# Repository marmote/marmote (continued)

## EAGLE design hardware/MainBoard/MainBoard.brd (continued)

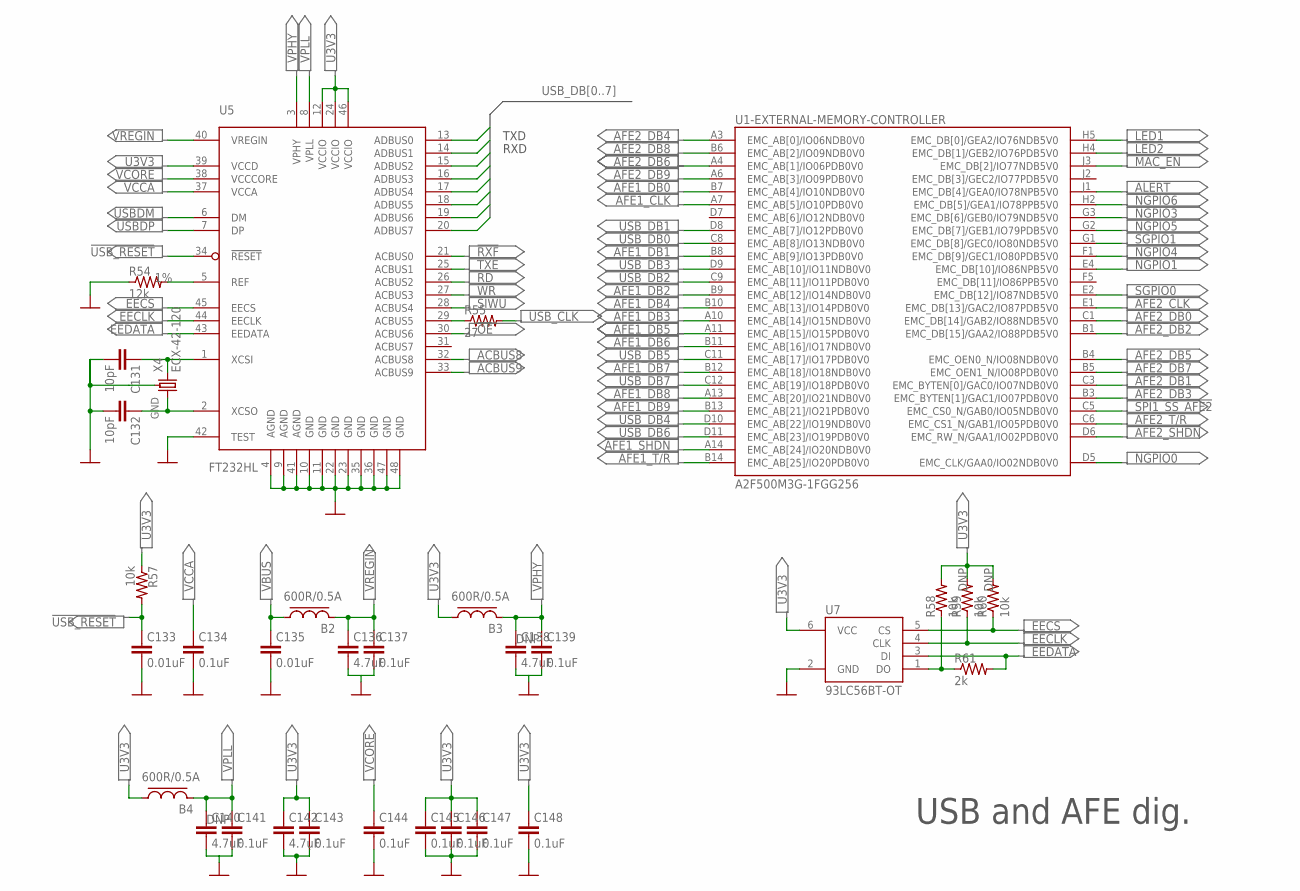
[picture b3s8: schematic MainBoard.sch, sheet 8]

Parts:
B2, B3, B4: 600R/0.5A; L0603; MPN BLM18EG601SN1D; DIGI-KEY# 490-3994-2-ND
C131, C132: 10pF; C0402
C133, C135: 0.01uF; C0402
C134, C137, C139, C141, C143, C144, C145, C146, C147, C148: 0.1uF; C0402
C136, C138, C140, C142: 4.7uF; C0402
R54: 12k; R0402; TOLERANCE 1%
R55: 27; R0402
R57, R58, R59, R60: 10k; R0402
R61: 2k; R0402
U1: A2F500M3G-1FGG256; FG256
U5: FT232HL; LQFP-48; MPN 768-1101-1-ND
U7: 93LC56BT-OT; SOT23-6L
X4: ECX-42-120; ECX-42

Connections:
!AFE1_SHDN: U1.A14 (EMC_AB[24]/IO20NDB0V0); also elsewhere on the board
!AFE2_SHDN: U1.D6 (EMC_RW_N/GAA1/IO02PDB0V0); also elsewhere on the board
!OE: U5.30 (ACBUS6); also elsewhere on the board
!RD: U5.26 (ACBUS2); also elsewhere on the board
!RXF: U5.21 (ACBUS0); also elsewhere on the board
!SIWU: U5.28 (ACBUS4); also elsewhere on the board
!SPI1_SS_AFE2: U1.C5 (EMC_CS0_N/GAB0/IO05NDB0V0); also elsewhere on the board
!TXE: U5.25 (ACBUS1); also elsewhere on the board
!USB_RESET: C133.1, R57.2, U5.34 (!RESET)
!WR: U5.27 (ACBUS3); also elsewhere on the board
ACBUS8: U5.32 (ACBUS8); also elsewhere on the board
ACBUS9: U5.33 (ACBUS9); also elsewhere on the board
AFE1_CLK: U1.A7 (EMC_AB[5]/IO10PDB0V0); also elsewhere on the board
AFE1_DB0: U1.B7 (EMC_AB[4]/IO10NDB0V0); also elsewhere on the board
AFE1_DB1: U1.B8 (EMC_AB[9]/IO13PDB0V0); also elsewhere on the board
AFE1_DB2: U1.B9 (EMC_AB[12]/IO14NDB0V0); also elsewhere on the board
AFE1_DB3: U1.A10 (EMC_AB[14]/IO15NDB0V0); also elsewhere on the board
AFE1_DB4: U1.B10 (EMC_AB[13]/IO14PDB0V0); also elsewhere on the board
AFE1_DB5: U1.A11 (EMC_AB[15]/IO15PDB0V0); also elsewhere on the board
AFE1_DB6: U1.B11 (EMC_AB[16]/IO17NDB0V0); also elsewhere on the board
AFE1_DB7: U1.B12 (EMC_AB[18]/IO18NDB0V0); also elsewhere on the board
AFE1_DB8: U1.A13 (EMC_AB[20]/IO21NDB0V0); also elsewhere on the board
AFE1_DB9: U1.B13 (EMC_AB[21]/IO21PDB0V0); also elsewhere on the board
AFE1_T/!R: U1.B14 (EMC_AB[25]/IO20PDB0V0); also elsewhere on the board
AFE2_CLK: U1.E1 (EMC_DB[13]/GAC2/IO87PDB5V0); also elsewhere on the board
AFE2_DB0: U1.C1 (EMC_DB[14]/GAB2/IO88NDB5V0); also elsewhere on the board
AFE2_DB1: U1.C3 (EMC_BYTEN[0]/GAC0/IO07NDB0V0); also elsewhere on the board
AFE2_DB2: U1.B1 (EMC_DB[15]/GAA2/IO88PDB5V0); also elsewhere on the board
AFE2_DB3: U1.B3 (EMC_BYTEN[1]/GAC1/IO07PDB0V0); also elsewhere on the board
AFE2_DB4: U1.A3 (EMC_AB[0]/IO06NDB0V0); also elsewhere on the board
AFE2_DB5: U1.B4 (EMC_OEN0_N/IO08NDB0V0); also elsewhere on the board
AFE2_DB6: U1.A4 (EMC_AB[1]/IO06PDB0V0); also elsewhere on the board
AFE2_DB7: U1.B5 (EMC_OEN1_N/IO08PDB0V0); also elsewhere on the board
AFE2_DB8: U1.B6 (EMC_AB[2]/IO09NDB0V0); also elsewhere on the board
AFE2_DB9: U1.A6 (EMC_AB[3]/IO09PDB0V0); also elsewhere on the board
AFE2_T/!R: U1.C6 (EMC_CS1_N/GAB1/IO05PDB0V0); also elsewhere on the board
ALERT: U1.J1 (EMC_DB[4]/GEA0/IO78NPB5V0); also elsewhere on the board
DGND: C131.2, C132.2, C133.2, C134.2, C135.2, C136.2, C137.2, C138.2, C139.2, C140.2, C141.2, C142.2, C143.2, C144.2, C145.2, C146.2, C147.2, C148.2, R54.1, U5.4 (AGND), U5.9 (AGND), U5.10 (GND), U5.11 (GND), U5.22 (GND), U5.23 (GND), U5.35 (GND), U5.36 (GND), U5.41 (AGND), U5.42 (TEST), U5.47 (GND), U5.48 (GND), U7.2 (GND), X4.2 (GND), X4.4 (GND); also elsewhere on the board
EECLK: R59.1, U5.44 (EECLK), U7.4 (CLK)
EECS: R60.1, U5.45 (EECS), U7.5 (CS)
EEDATA: R61.2, U5.43 (EEDATA), U7.3 (DI)
EEDO: R58.1, R61.1, U7.1 (DO)
LED1: U1.H5 (EMC_DB[0]/GEA2/IO76NDB5V0); also elsewhere on the board
LED2: U1.H4 (EMC_DB[1]/GEB2/IO76PDB5V0); also elsewhere on the board
MAC_EN: U1.J3 (EMC_DB[2]/IO77NDB5V0); also elsewhere on the board
NGPIO0: U1.D5 (EMC_CLK/GAA0/IO02NDB0V0); also elsewhere on the board
NGPIO1: U1.E4 (EMC_DB[10]/IO86NPB5V0); also elsewhere on the board
NGPIO3: U1.G3 (EMC_DB[6]/GEB0/IO79NDB5V0); also elsewhere on the board
NGPIO4: U1.F1 (EMC_DB[9]/GEC1/IO80PDB5V0); also elsewhere on the board
NGPIO5: U1.G2 (EMC_DB[7]/GEB1/IO79PDB5V0); also elsewhere on the board
NGPIO6: U1.H2 (EMC_DB[5]/GEA1/IO78PPB5V0); also elsewhere on the board
SGPIO0: U1.E2 (EMC_DB[12]/IO87NDB5V0); also elsewhere on the board
SGPIO1: U1.G1 (EMC_DB[8]/GEC0/IO80NDB5V0); also elsewhere on the board
U3V3: B3.1, B4.1, C142.1, C143.1, C145.1, C146.1, C147.1, C148.1, R57.1, R58.2, R59.2, R60.2, U5.12 (VCCIO), U5.24 (VCCIO), U5.39 (VCCD), U5.46 (VCCIO), U7.6 (VCC)
UREF: R54.2, U5.5 (REF)
USBDM: U5.6 (DM); also elsewhere on the board
USBDP: U5.7 (DP); also elsewhere on the board
USB_CLK: R55.2; also elsewhere on the board
USB_CLKF: R55.1, U5.29 (ACBUS5)
USB_DB0: U1.C8 (EMC_AB[8]/IO13NDB0V0), U5.13 (ADBUS0); also elsewhere on the board
USB_DB1: U1.D8 (EMC_AB[7]/IO12PDB0V0), U5.14 (ADBUS1); also elsewhere on the board
USB_DB2: U1.C9 (EMC_AB[11]/IO11PDB0V0), U5.15 (ADBUS2)
USB_DB3: U1.D9 (EMC_AB[10]/IO11NDB0V0), U5.16 (ADBUS3)
USB_DB4: U1.D10 (EMC_AB[22]/IO19NDB0V0), U5.17 (ADBUS4)
USB_DB5: U1.C11 (EMC_AB[17]/IO17PDB0V0), U5.18 (ADBUS5)
USB_DB6: U1.D11 (EMC_AB[23]/IO19PDB0V0), U5.19 (ADBUS6)
USB_DB7: U1.C12 (EMC_AB[19]/IO18PDB0V0), U5.20 (ADBUS7)
UXCSI: C131.1, U5.1 (XCSI), X4.3 (2)
UXCSO: C132.1, U5.2 (XCSO), X4.1
VBUS: B2.1, C135.1; also elsewhere on the board
VCCA: C134.1, U5.37 (VCCA)
VCORE: C144.1, U5.38 (VCCCORE)
VPHY: B3.2, C138.1, C139.1, U5.3 (VPHY)
VPLL: B4.2, C140.1, C141.1, U5.8 (VPLL)
VREGIN: B2.2, C136.1, C137.1, U5.40 (VREGIN)

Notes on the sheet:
TXD
RXD

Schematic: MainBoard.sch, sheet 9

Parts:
LED1: LED-MGC-3010; LED1208-RA
LED2: LED-ECK-3010; LED1208-RA
R62, R63, R64, R65: 39; R0402
R66, R72, R73: 100; R0402
R67: 330; R0402
R68, R69: 100k; R0402
R70, R71: 4.7k; R0402
U1: A2F500M3G-1FGG256; FG256

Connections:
!OE: U1.E16 (GDC0/IO38NDB1V0); also elsewhere on the board
!RD: U1.D14 (GCB2/IO33PDB1V0); also elsewhere on the board
!RXF: U1.D13 (GBB2/IO27NPB1V0); also elsewhere on the board
!SIWU: U1.E14 (GCB1/IO34PDB1V0); also elsewhere on the board
!SPI1_SS_AFE1: U1.C14 (GBA2/IO27PPB1V0); also elsewhere on the board
!TXE: U1.D15 (IO33NDB1V0); also elsewhere on the board
!WR: U1.E15 (GDC1/IO38PDB1V0); also elsewhere on the board
ACBUS8: U1.E12 (GCA1/IO36PDB1V0); also elsewhere on the board
ACBUS9: U1.F12 (GCA0/IO36NDB1V0); also elsewhere on the board
D3V3: R66.2, R67.2, R68.2, R69.2, R70.2, R71.2; also elsewhere on the board
I2C0_SCL: R70.1, R72.2; also elsewhere on the board
I2C0_SCLI: R72.1, U1.J12 (I2C_0_SCL/GPIO_23)
I2C0_SDA: R71.1, R73.2; also elsewhere on the board
I2C0_SDAI: R73.1, U1.J13 (I2C_0_SDA/GPIO_22)
LED1: LED1.1 (C); also elsewhere on the board
LED1H: LED1.2 (A), R66.1
LED2: LED2.1 (C); also elsewhere on the board
LED2H: LED2.2 (A), R67.1
NGPIO2: U1.F3 (GFB2/IO85NDB5V0); also elsewhere on the board
NGPIO7: U1.E3 (GFA2/IO85PDB5V0); also elsewhere on the board
REF_CLK+: U1.C15 (GCA2/IO28PDB1V0); also elsewhere on the board
REF_CLK-: U1.C16 (IO28NDB1V0); also elsewhere on the board
SPI0_MISO: U1.M16 (SPI_0_DI/GPIO_17); also elsewhere on the board
SPI0_MOSI: U1.N16 (SPI_0_DO/GPIO_16); also elsewhere on the board
SPI0_SCLK: U1.M15 (SPI_0_CLK/GPIO_18); also elsewhere on the board
SPI0_SS: R68.1, U1.M13 (SPI_0_SS/GPIO_19); also elsewhere on the board
SPI1_MISO: U1.L15 (SPI_1_DI/GPIO_25); also elsewhere on the board
SPI1_MOSI: U1.L12 (SPI_1_DO/GPIO_24); also elsewhere on the board
SPI1_SCLK: U1.L14 (SPI_1_CLK/GPIO_26); also elsewhere on the board
SPI1_SS: R69.1, U1.L13 (SPI_1_SS/GPIO_27); also elsewhere on the board
UART0_RXD: R63.2, U1.K12 (UART_0_RXD/GPIO_21)
UART0_TXD: R62.2, U1.K16 (UART_0_TXD/GPIO_20)
UART1_RXD: R65.1; also elsewhere on the board
UART1_RXDI: R65.2, U1.K15 (UART_1_RXD/GPIO_29)
UART1_TXD: R64.1; also elsewhere on the board
UART1_TXDI: R64.2, U1.K14 (UART_1_TXD/GPIO_28)
USB_CLK: U1.F14 (GCB0/IO34NDB1V0); also elsewhere on the board
USB_DB0: R63.1; also elsewhere on the board
USB_DB1: R62.1; also elsewhere on the board

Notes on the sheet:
ORANGE
GREEN

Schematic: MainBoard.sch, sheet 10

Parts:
J1: CON-ZX62R-B-5P; ZX62R-B-5P
J3: CON-FTSH-105-01-L-DV-K; FTSH-105-01-L-DV-K
J4: CON-71741-2184-BOT; 71742-3003-BOT
J5: CON-71741-2184-TOP; 71741-0002; MPN 71741-0002; DIGI-KEY# WM3498CT-ND
M1, M2, M3, M4: MOUNT-HOLE3.3; 3,3
M5, M6, M7, M8, M9, M10, M11, M12: FIDUCIAL1X2; FIDUCIAL-1X2
R74, R75: 0; R0402
R76: 0; R0603
TP1, TP2: TESTPOINT-YELLOW; TESTPOINT
TP3, TP4: TESTPOINT-GREEN; TESTPOINT
U4: USBLC6-2SC6; SOT23-6L

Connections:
!WAKEUP: J4.27, J5.27; also elsewhere on the board
A1V5: J4.79, J4.80, J5.79, J5.80; also elsewhere on the board
A3V3: J4.81, J4.82, J5.81, J5.82; also elsewhere on the board
ADC1+: J5.46; also elsewhere on the board
ADC1-: J5.44; also elsewhere on the board
ADC2+: J5.52; also elsewhere on the board
ADC2-: J5.50; also elsewhere on the board
ADC3+: J5.70; also elsewhere on the board
ADC3-: J5.68; also elsewhere on the board
ADC4+: J5.76; also elsewhere on the board
ADC4-: J5.74; also elsewhere on the board
AGND: J4.29, J4.30, J4.35, J4.36, J4.41, J4.42, J4.47, J4.48, J4.53, J4.54, J4.59, J4.60, J4.65, J4.66, J4.71, J4.72, J4.77, J4.78, J4.83, J4.84, J5.29, J5.30, J5.35, J5.36, J5.41, J5.42, J5.47, J5.48, J5.53, J5.54, J5.59, J5.60, J5.65, J5.66, J5.71, J5.72, J5.77, J5.78, J5.83, J5.84, R76.2, TP3.1, TP4.1; also elsewhere on the board
ALERT: J4.25, J5.25; also elsewhere on the board
D1V5: J4.7, J4.8, J5.7, J5.8; also elsewhere on the board
D3V3: J4.5, J4.6, J5.5, J5.6; also elsewhere on the board
DAC1+: J5.34; also elsewhere on the board
DAC1-: J5.32; also elsewhere on the board
DAC2+: J5.40; also elsewhere on the board
DAC2-: J5.38; also elsewhere on the board
DAC3+: J5.58; also elsewhere on the board
DAC3-: J5.56; also elsewhere on the board
DAC4+: J5.64; also elsewhere on the board
DAC4-: J5.62; also elsewhere on the board
DGND: J1.5 (GND), J3.2, J3.10, J4.1, J4.2, J4.9, J4.10, J5.1, J5.2, J5.9, J5.10, R76.1, TP1.1, TP2.1, U4.2 (GND); also elsewhere on the board
I2C0_SCL: J4.26, J5.26; also elsewhere on the board
I2C0_SDA: J4.28, J5.28; also elsewhere on the board
NGPIO0: J5.11; also elsewhere on the board
NGPIO1: J5.13; also elsewhere on the board
NGPIO2: J5.15; also elsewhere on the board
NGPIO3: J5.17; also elsewhere on the board
NGPIO4: J5.19; also elsewhere on the board
NGPIO5: J5.21; also elsewhere on the board
NGPIO6: J5.23; also elsewhere on the board
NGPIO7: J5.16; also elsewhere on the board
REF_CLK+: J5.14; also elsewhere on the board
REF_CLK-: J5.12; also elsewhere on the board
SF_ABPS0: J5.75; also elsewhere on the board
SF_ABPS1: J5.73; also elsewhere on the board
SF_ADC0: J5.49; also elsewhere on the board
SF_ADC1: J5.51; also elsewhere on the board
SF_ADC2: J5.55; also elsewhere on the board
SF_ADC3: J5.57; also elsewhere on the board
SF_ADC4: J5.45; also elsewhere on the board
SF_ADC5: J5.43; also elsewhere on the board
SF_ADC6: J5.39; also elsewhere on the board
SF_ADC7: J5.37; also elsewhere on the board
SF_CM0: J5.69; also elsewhere on the board
SF_CM1: J5.63; also elsewhere on the board
SF_DAC0: J5.33; also elsewhere on the board
SF_DAC1: J5.31; also elsewhere on the board
SF_TM0: J5.67; also elsewhere on the board
SF_TM1: J5.61; also elsewhere on the board
SGPIO0: J4.17; also elsewhere on the board
SGPIO1: J4.19; also elsewhere on the board
SPI0_MISO: J4.22; also elsewhere on the board
SPI0_MOSI: J4.20; also elsewhere on the board
SPI0_SCLK: J4.18; also elsewhere on the board
SPI0_SS: J4.24; also elsewhere on the board
SPI1_MISO: J5.22; also elsewhere on the board
SPI1_MOSI: J5.20; also elsewhere on the board
SPI1_SCLK: J5.18; also elsewhere on the board
SPI1_SS: J5.24; also elsewhere on the board
TCK: J3.1; also elsewhere on the board
TDI: J3.9; also elsewhere on the board
TDO: J3.3; also elsewhere on the board
TMS: J3.5; also elsewhere on the board
TRST: J3.8; also elsewhere on the board
UART1_RXD: J4.23; also elsewhere on the board
UART1_TXD: J4.21; also elsewhere on the board
USBDM: R74.2; also elsewhere on the board
USBDM-IN: J1.2 (D-), U4.6 (IO1)
USBDM-OUT: R74.1, U4.1 (IO1)
USBDP: R75.2; also elsewhere on the board
USBDP-IN: J1.3 (D+), U4.4 (IO2)
USBDP-OUT: R75.1, U4.3 (IO2)
VBUS: J1.1 (VBUS), U4.5 (VBUS); also elsewhere on the board
VJTAG: J3.6; also elsewhere on the board
VPUMP: J3.7; also elsewhere on the board
VSUP: J4.3, J4.4, J5.3, J5.4

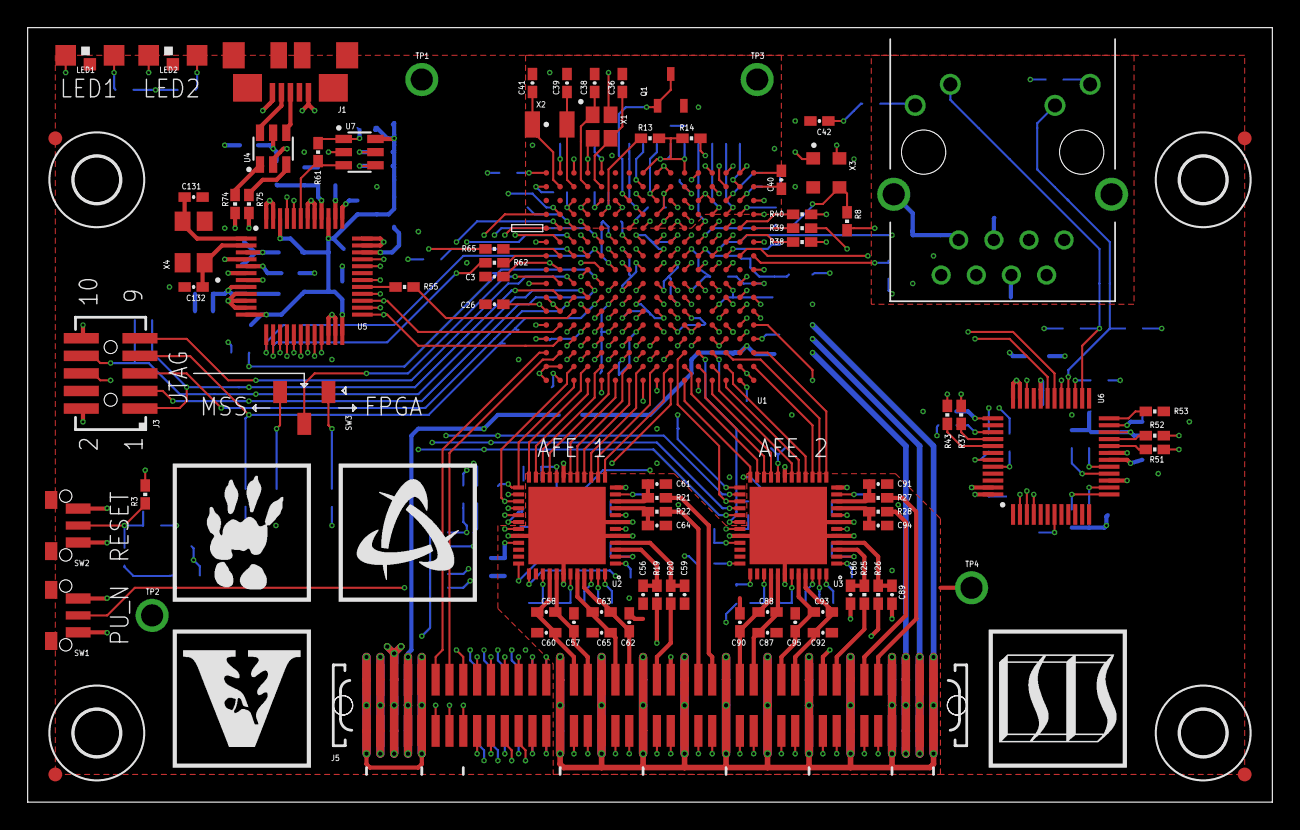
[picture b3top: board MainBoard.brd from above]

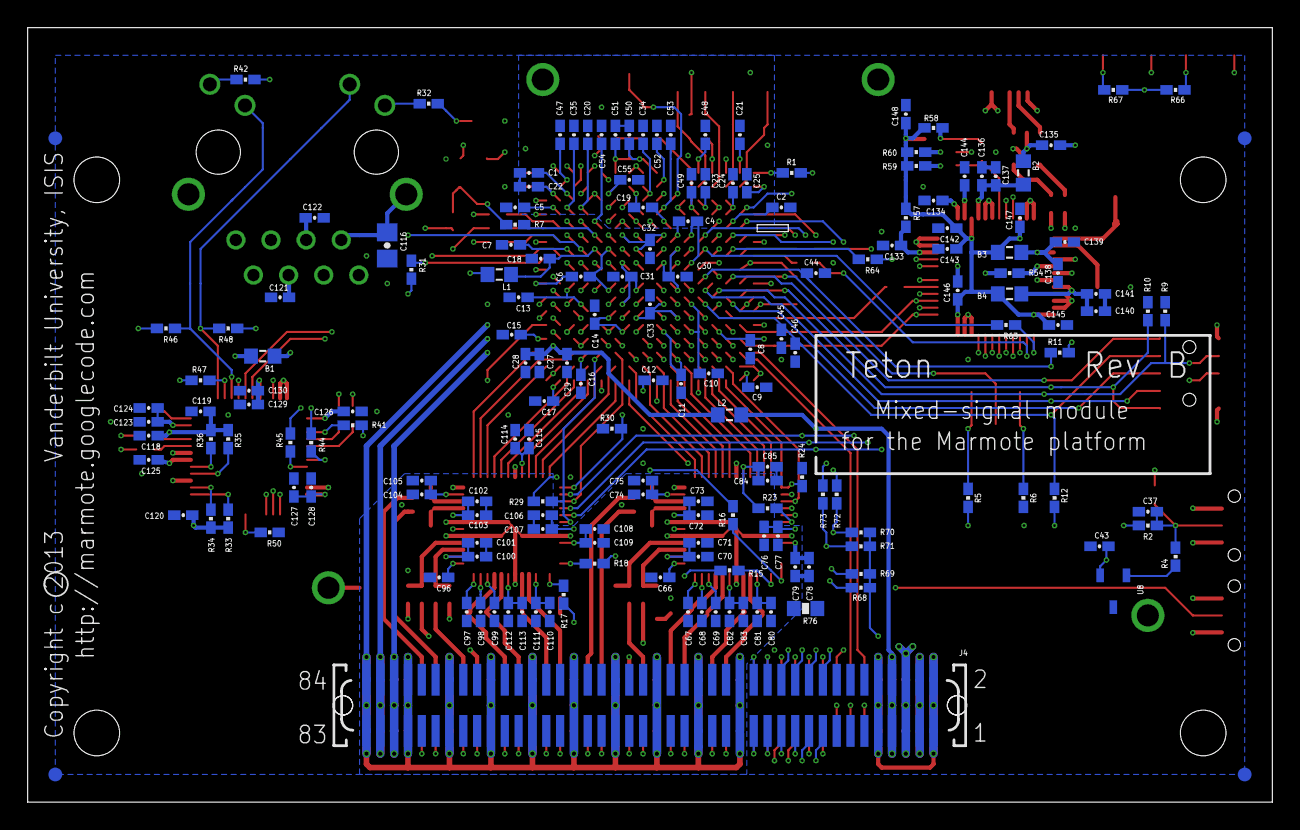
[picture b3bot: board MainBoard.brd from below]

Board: 6 copper layers, 90.0 x 56.0 mm, 270 parts (177 on the bottom side), 221 nets.

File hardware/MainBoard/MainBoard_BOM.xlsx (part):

Bill of Materials for 'Marmote - Main Board (Teton)'
Item # | Reference | Value | Package | Manufacturer | Manufacturer Part # | Supplier | Supplier Part # | Details | Qty | Unit Price | Total Cost
1 | B1 | 70R/4A | BEAD-BLM18SG700TN1D0603 | Murata | BLM18SG700TN1D | Digi-Key | 490-5224-1-ND | FERRITE CHIP 70 OHM 4000MA 0603 | 1 | 0.38 | 0.38
2 | B2, B3, B4 | 600R/0.5A | BEAD-BLM18EG601SN1D0603 | Murata | BLM18EG601SN1D | Digi-Key | 490-3994-2-ND | FILTER CHIP 600 OHM 500MA 0603 | 3 | 0.38 | 1.1400000000000001
3 | C1, C40, C70, C72, C74, C76, C78, C80, C82, C84, C100, C102, C104, C106, C108, 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 | 2.2uF | C0402 | Taiyo Yuden | LMK105BJ225MV-F | Digi-Key | 587-3153-1-ND | CAP CER 2.2UF 10V 20% X5R 0402 | 18 | 0.3 | 5.3999999999999995
4 | C2, C3, C4, C5, C6, C7, C8, C9, C10, C11, C12, C13, C14, C15, C16, C17, C18, C1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 | 0.1uF | C0402 | TDK | C1005X7R1C104K | Digi-Key | 445-4952-1-ND | CAP CER 0.1UF 16V 10% X7R 0402 | 73 | 0.09 | 6.5699999999999994
5 | C29, C42, C46, C133, C135 | 0.01uF | C0402 | TDK | C1005X7R1C103M | Digi-Key | 445-4943-1-ND | CAP CER 10000PF 16V 20% X7R 0402 | 5 | 0.08 | 0.4
6 | C36, C38, C131, C132 | 10pF | C0402 | TDK | C1005C0G1H100D | Digi-Key | 445-1235-1-ND | CAP CER 10PF 50V NP0 0402 | 4 | 0.08 | 0.32
7 | C39, C41 | 4pF | C0402 | TDK | CGA2B2C0G1H040C | Digi-Key | 445-5576-1-ND | CAP CER 4PF 50V NP0 0402 | 2 | 0.2 | 0.4
8 | C45, C66, C67, C68, C96, C97, C98 | 0.33uF | C0402 | TDK | C1005X5R1C334K | Digi-Key | 445-4974-1-ND | CAP CER 0.33UF 16V 10% X5R 0402 | 7 | 0.28000000000000003 | 1.9600000000000002
9 | C47, C48, C52, C53, C54, C55, C57, C58, C60, C62, C63, C65, C87, C88, C90, C92,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 | DNP | C0402 |  |  |  |  | CAPACITOR | 18 |  | 0
10 | C56, C59, C61, C64, C86, C89, C91, C94 | 22pF | C0402 | TDK | C1005C0G1H220J | Digi-Key | 445-1239-1-ND | CAP CER 22PF 50V 5% NP0 0402 | 8 | 0.08 | 0.64
11 | C116 | 1000pF | C0805 | TDK | C2012X7R2E102K | Digi-Key | 445-2277-1-ND | CAP CER 1000PF 250V 10% X7R 0805 | 1 | 0.17 | 0.17
12 | C27, C49, C50, C51, C123, C127, C129, C136, C138, C140, C142 | 4.7uF | C0402 | TDK | C1005X5R1A475M | Digi-Key | 445-8023-1-ND | CAP CER 4.7UF 10V 20% X5R 0402 | 11 | 0.53 | 5.83
13 | J1 | CON-ZX62R-B-5P | CON-ZX62R-B-5P | Hirose | ZX62R-B-5P | Digi-Key | H11574CT-ND | ZX62R-B-5P | 1 | 1.6 | 1.6
14 | J2 | CON-RJ45-J0011D21BNL | CON-RJ45-J0011D21BNL | Pulse Electronics Corporation | J0011D21BNL | Digi-Key | 553-1485-ND | CONN PULSEJACK 1PORT 10/100B-TX | 1 | 7.1 | 7.1
15 | J3 | CON-FTSH-105-01-L-DV-K | CON-FTSH-105-01-L-DV-K | Samtec | FTSH-105-01-L-DV-K | Digi-Key | FTSH-105-01-L-DV-K-ND | CONN HEADER 10 POS DUAL .05" SMD | 1 | 3.45 | 3.45
16 | J4 | CON-71741-2184-BOT | CON-71741-2184-BOT | Molex | 71742-3003 | Digi-Key | WM3499CT-ND | MEZZANINE 1MM BTB RECPT 84CKT | 1 | 5.81 | 5.81
17 | J5 | CON-71741-2184-TOP | CON-71741-2184-TOP | Molex | 71741-0002 | Digi-Key | WM3498CT-ND | MEZZANINE 1MM BTB PLUG 84CKT | 1 | 6.24 | 6.24
18 | L1, L2 | 33nH | L0603 | JW Miller | PM0603-33NJ-RC | Digi-Key | M8487CT-ND | INDUCTOR CHIP 33NH 5% SMD | 2 |  | 0
19 | LED1 | LED-MGC-3010 | LED-MGC-3010 | Kingbright | APECVA3010MGC | Digi-Key | 754-1364-1-ND | LED 3.0X1.0MM 568NM GRN RA SMD | 1 | 0.6 | 0.6
20 | LED2 | LED-ECK-3010 | LED-ECK-3010 | Kingbright | APECVA3010SECK | Digi-Key | 754-1367-1-ND | LED 3X1MM 601NM ORN RA CHIP SMD | 1 | 0.33 | 0.33
21 | Q1 | MMBT3904 | MMBT3904 | Fairchild Semiconductor | MMBT3904 | Digi-Key | MMBT3904FSCT-ND | TRANSISTOR GP NPN AMP SOT-23 | 1 | 0.37 | 0.37
22 | R1, R2, R57, R58, R59, R60 | 10k | R0402 | Rohm | MCR01MRTF1002 | Digi-Key | RHM10.0KCDCT-ND | RES 10.0K OHM 1/16W 1% 0402 SMD | 6 | 2.3E-2 | 0.13800000000000001
23 | R19, R20, R21, R22, R25, R26, R27, R28 | 24.9 | R0402 | Vishay Dale | CRCW040224R9FKED | Digi-Key | 541-24.9LCT-ND | RES 24.9 OHM 1/16W 1% 0402 SMD | 8 | 8.3000000000000004E-2 | 0.66400000000000003
24 | R23, R24, R29, R30, R68, R69 | 100k | R0402 | Rohm | TRR01MZPF1003 | Digi-Key | RHM100KBHCT-ND | RES 100K OHM 1/16W 1% 0402 SMD | 6 | 0.123 | 0.73799999999999999
25 | R3, R7, R8, R62, R63, R64, R65 | 39 | R0402 | Rohm | MCR01MZPF39R0 | Digi-Key | RHM39.0LCT-ND | RES 39.0 OHM 1/16W 1% 0402 SMD | 7 | 2.5999999999999999E-2 | 0.182
26 | R31 | 1.5k | R0402 | Rohm | TRR01MZPF1501 | Digi-Key | RHM1.50KBHCT-ND | RES 1.50K OHM 1/16W 1% 0402 SMD | 1 | 0.123 | 0.123
27 | R32, R42 | 100 | R0402 | Rohm | TRR01MZPF1000 | Digi-Key | RHM100BHCT-ND | RES 100 OHM 1/16W 1% 0402 SMD | 2 | 0.20100000000000001 | 0.40200000000000002
28 | R33, R34, R35, R36 | 49.9 | R0402 | Rohm | MCR01MRTF49R9 | Digi-Key | RHM49.9CDCT-ND | RES 49.9 OHM 1/16W 1% 0402 SMD | 4 | 2.3E-2 | 9.1999999999999998E-2
29 | R37, R38, R39, R40, R43, R44, R45 | 22 | R0402 | Rohm | MCR01MRTF22R0 | Digi-Key | RHM22.0CDCT-ND | RES 22.0 OHM 1/16W 1% 0402 SMD | 7 | 2.3E-2 | 0.161
30 | R4, R11, R12, R13, R15, R16, R17, R18, R74, R75 | 0 | R0402 | Rohm | TRR01MZPJ000 | Digi-Key | RHM0.0BICT-ND | RES 0.0 OHM 1/16W 0402 SMD | 11 | 0.18099999999999999 | 1.9909999999999999
30 | R14 | DNP | R0402 | Rohm | TRR01MZPJ000 | Digi-Key | RHM0.0BICT-ND | RES 0.0 OHM 1/16W 0402 SMD | 1 | 0.18099999999999999 | 0.18099999999999999
31 | R41, R46, R47, R48, R50, R51, R52 | 2.2k | R0402 | Rohm | MCR01MRTF2201 | Digi-Key | RHM2.20KCDCT-ND | RES 2.20K OHM 1/16W 1% 0402 SMD | 7 | 2.3E-2 | 0.161
32 | R5, R6, R9, R10 | 1k | R0402 | Rohm | TRR01MZPF1001 | Digi-Key | RHM1.00KBHCT-ND | RES 1.00K OHM 1/16W 1% 0402 SMD | 4 | 0.123 | 0.49199999999999999
33 | R53 | 4.87k | R0402 | Vishay Dale | CRCW04024K87FKED | Digi-Key | 541-4.87KLCT-ND | RES 4.87K OHM 1/16W 1% 0402 SMD | 1 | 8.3000000000000004E-2 | 8.3000000000000004E-2
34 | R54 | 12k | R0402 | Vishay Dale | CRCW040212K0FKED | Digi-Key | 541-12.0KLCT-ND | RES 12.0K OHM 1/16W 1% 0402 SMD | 1 | 8.3000000000000004E-2 | 8.3000000000000004E-2
35 | R55 | 27 | R0402 | Vishay Dale | CRCW040227R0FKED | Digi-Key | 541-27.0LCT-ND | RES 27.0 OHM 1/16W 1% 0402 SMD | 1 | 8.3000000000000004E-2 | 8.3000000000000004E-2
36 | R56 | 39k | R0402 | Vishay Dale | CRCW040239K0FKED | Digi-Key | 541-39.0KLCT-ND | RES 39.0K OHM 1/16W 1% 0402 SMD | 1 | 8.3000000000000004E-2 | 8.3000000000000004E-2
37 | R61 | 2k | R0402 | Vishay Dale | CRCW04022K00FKED | Digi-Key | 541-2.00KLCT-ND | RES 2.00K OHM 1/16W 1% 0402 SMD | 1 | 8.3000000000000004E-2 | 8.3000000000000004E-2
38 | R66, R72, R73 | 100 | R0402 | Vishay Dale | CRCW0402100RFKED | Digi-Key | 541-100LCT-ND | RES 100 OHM 1/16W 1% 0402 SMD | 3 | 8.3000000000000004E-2 | 0.249
39 | R67 | 330 | R0402 | Vishay Dale | CRCW0402330RFKED | Digi-Key | 541-330LCT-ND | RES 330 OHM 1/16W 1% 0402 SMD | 1 | 8.3000000000000004E-2 | 8.3000000000000004E-2
40 | R70, R71 | 4.7k | R0402 | Vishay Dale | CRCW04024K70FKED | Digi-Key | 541-4.70KLCT-ND | RES 4.70K OHM 1/16W 1% 0402 SMD | 2 | 8.3000000000000004E-2 | 0.16600000000000001
41 | R76 | DNP | R0603 |  |  |  |  | RESISTOR | 1 |  | 0
42 | SW1, SW2 | SWITCH-ESWITCH-TL3340G | SWITCH-ESWITCH-TL3340G | E-Switch | TL3340AF160QG | Digi-Key | EG4627CT-ND | SWITCH TACTILE SPST-NO 0.05A 12V | 2 | 0.29099999999999998 | 0.58199999999999996
43 | SW3 | SWITCH-CJS-1200-1200 | J-Lead | CJS | CJS-1200TA | Digi-Key | 563-1021-1-ND | CJS-1200 SPDT Switch | 1 | 0.97 | 0.97
44 | TP1, TP2 | TESTPOINT-YELLOW | TESTPOINT-YELLOW | Keystone | 5009 | Digi-Key | 5009K-ND | TEST POINT PC COMPACT .063"D YLW | 2 | 0.35 | 0.7
45 | TP3, TP4 | TESTPOINT-GREEN | TESTPOINT-GREEN | Keystone | 5121 | Digi-Key | 5121K-ND | TEST POINT PC COMPACT T/H GREEN | 2 | 0.35 | 0.7
46 | U1 | A2F500M3G-1FGG256 | A2F500M3G-1FGG256 | Microsemi | A2F500M3G-1FGG256 | Digi-Key | 1100-1007-ND | IC FPGA 512K FLASH 256FPBGA | 1 | 53.91 | 53.91
47 | U2, U3 | MAX19706-T4877-4 | MAX19706-T4877-4 | Maxim | MAX19706ETM+ | Digi-Key | MAX19706ETM+-ND | IC ANLG FRNT END 48-TQFN | 2 | 20.09 | 40.18
48 | U4 | USBLC6-2SC6 | USBLC6-2SC6 | STMicroelectronics | USBLC6-2SC6 | Digi-Key | 497-5235-1-ND | USBLC6-2SC6 | 1 | 0.95 | 0.95
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
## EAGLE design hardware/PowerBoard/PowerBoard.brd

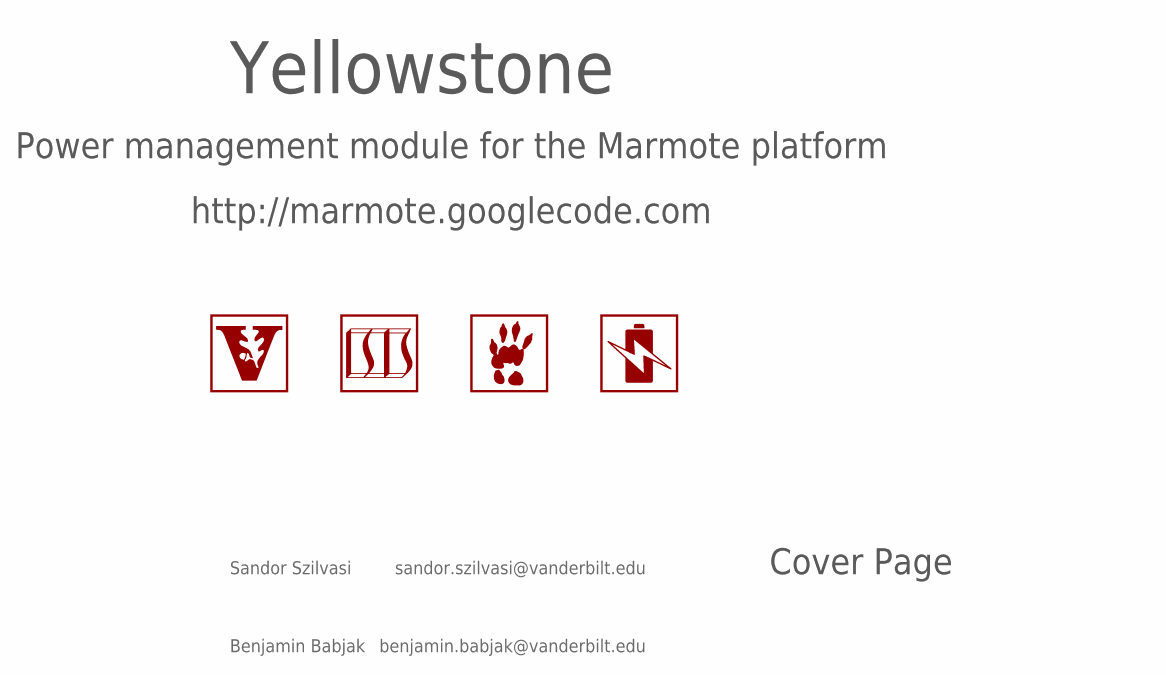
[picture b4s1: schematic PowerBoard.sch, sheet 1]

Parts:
LOGO1: LOGO-ISIS-600MIL-10MM-SS; LOGO-ISIS-10MM-SILKSCREEN
LOGO2: LOGO-BATTERY-600MIL-10MM-SS; LOGO-BATTERY-10MM-SILKSCREEN
LOGO5: LOGO-VANDERBILT-600MIL-10MM-SS; LOGO-VANDERBILT-10MM-SILKSCREEN
LOGO6: LOGO-MARMOTE-600MIL-10MM-SS; LOGO-MARMOTE-10MM-SILKSCREEN

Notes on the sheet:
Power management module for the Marmote platform
http://marmote.googlecode.com

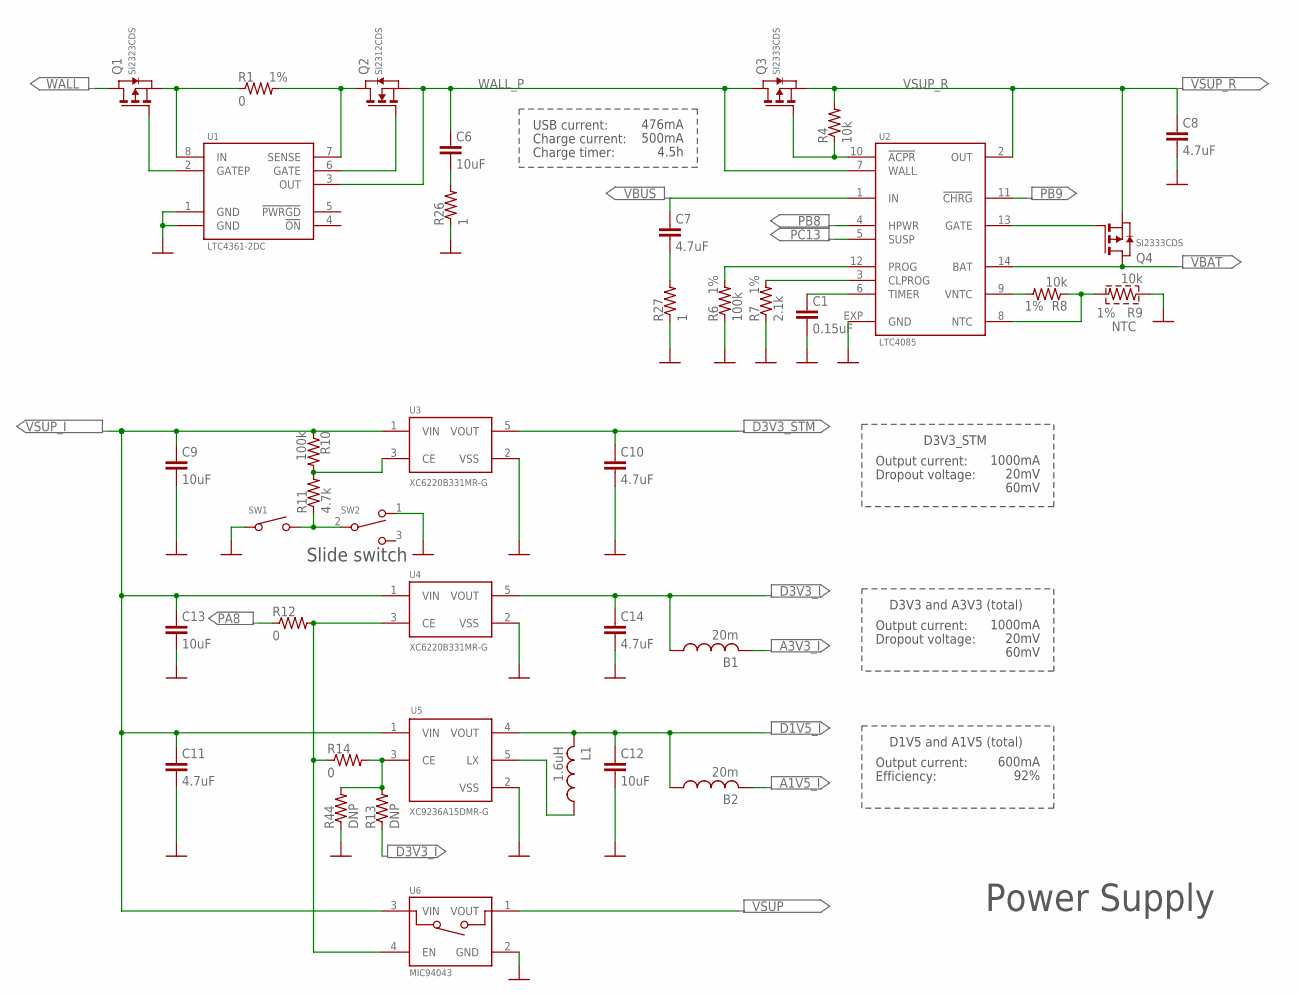
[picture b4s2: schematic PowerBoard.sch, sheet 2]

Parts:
B1, B2: 20m; L0603
C1: 0.15uF; C0603
C6, C9, C12, C13: 10uF; C0603
C7, C8, C10, C11, C14: 4.7uF; C0603
L1: 1.6uH; 4X4MM
Q1: SI2323CDS; SOT23-3L
Q2: SI2312CDS; SOT23-3L
Q3, Q4: SI2333CDS; SOT23-3L
R1: 0; R0603; TOLERANCE 1%
R4: 10k; R0603
R6: 100k; R0603; TOLERANCE 1%
R7: 2.1k; R0603; TOLERANCE 1%
R8, R9: 10k; R0603; TOLERANCE 1%
R10: 100k; R0603
R11: 4.7k; R0603
R12, R14: 0; R0603
R13, R44: DNP; R0603
R26, R27: 1; R0603
SW1: SWITCH-SPST; S2B-PH-SM4-TB
SW2: SWITCH-MS12ASG30; MS12ASX30
U1: LTC4361-2DC; DFN-8
U2: LTC4085; DFN-14
U3, U4: XC6220B331MR-G; SOT25
U5: XC9236A15DMR-G; SOT25
U6: MIC94043; MLF-4

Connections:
!ACPR: Q3.1 (G), R4.1, U2.10 (!ACPR)
A1V5_I: B2.2; also elsewhere on the board
A3V3_I: B1.2; also elsewhere on the board
CLPROG: R7.2, U2.3 (CLPROG)
D1V5-EN: R13.2, R14.2, R44.2, U5.3 (CE)
D1V5_I: B2.1, C12.1, L1.2, U5.4 (VOUT); also elsewhere on the board
D3V3_I: B1.1, C14.1, R13.1, U4.5 (VOUT); also elsewhere on the board
D3V3_STM: C10.1, U3.5 (VOUT); also elsewhere on the board
D3V3_STM-EN: R10.2, R11.2, U3.3 (CE)
D3V3_STM-EN-SW: R11.1, SW1.2 (1A), SW2.2
DGND: C1.2, C8.2, C9.2, C10.2, C11.2, C12.2, C13.2, C14.2, R6.1, R7.1, R9.2 (4), R26.1, R27.1, R44.1, SW1.1, SW2.1, U1.1 (GND), U1.EXP (GND), U2.EXP (GND), U3.2 (VSS), U4.2 (VSS), U5.2 (VSS), U6.2 (GND); also elsewhere on the board
GATE1: Q2.1 (G), U1.6 (GATE)
GATE2: Q4.1 (G), U2.13 (GATE)
GATEP: Q1.1 (G), U1.2 (GATEP)
IN: Q1.2 (S), R1.1, U1.8 (IN)
unnamed: C7.2, R27.2
unnamed: C6.2, R26.2
unnamed: L1.1, U5.5 (LX)
unnamed: Q2.3 (D), R1.2, U1.7 (SENSE)
NTC: R8.1, R9.1 (3), U2.8 (NTC)
PA8: R12.1; also elsewhere on the board
PA8-EN: R12.2, R14.1, U4.3 (CE), U6.4 (EN); also elsewhere on the board
PB8: U2.4 (HPWR); also elsewhere on the board
PB9: U2.11 (!CHRG); also elsewhere on the board
PC13: U2.5 (SUSP); also elsewhere on the board
PROG: R6.2, U2.12 (PROG)
TIMER: C1.1, U2.6 (TIMER)
VBAT: Q4.3 (D), U2.14 (BAT); also elsewhere on the board
VBUS: C7.1, U2.1 (IN); also elsewhere on the board
VNTC: R8.2, U2.9 (VNTC)
VSUP: U6.1 (VOUT); also elsewhere on the board
VSUP_I: C9.1, C11.1, C13.1, R10.1, U3.1 (VIN), U4.1 (VIN), U5.1 (VIN), U6.3 (VIN); also elsewhere on the board
VSUP_R: C8.1, Q3.2 (S), Q4.2 (S), R4.2, U2.2 (OUT); also elsewhere on the board
WALL: Q1.3 (D); also elsewhere on the board
WALL_P: C6.1, Q2.2 (S), Q3.3 (D), U1.3 (OUT), U2.7 (WALL)

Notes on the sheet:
USB current:
Charge current:
476mA
500mA
Charge timer:
4.5h
Output current:
Dropout voltage:
1000mA
20mV
60mV
D3V3 and A3V3 (total)
Efficiency:
600mA
92%
D1V5 and A1V5 (total)
D3V3_STM
Slide switch

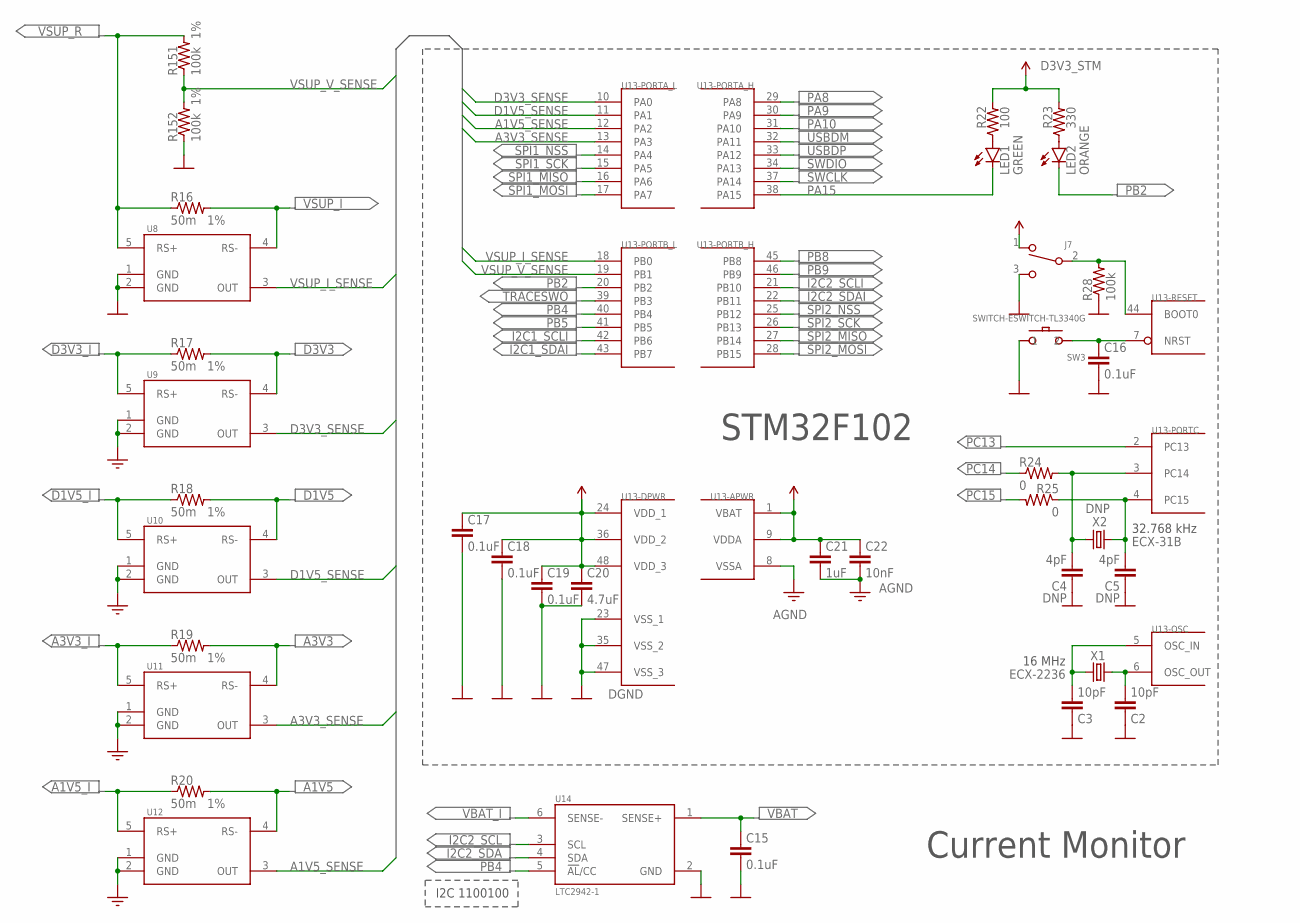
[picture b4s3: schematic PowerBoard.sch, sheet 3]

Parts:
C2, C3: 10pF; C0603
C4, C5: 4pF; C0603
C15, C16, C17, C18, C19: 0.1uF; C0603
C20: 4.7uF; C0603
C21: 1uF; C0603
C22: 10nF; C0603
J7: SWITCH-CJS-1200-1200; SWITCH-DIP-CJS
LED1: GREEN; LED1208-RA
LED2: ORANGE; LED1208-RA
R16, R17, R18, R19, R20: 50m; R0603; TOLERANCE 1%
R22: 100; R0603
R23: 330; R0603
R24, R25: 0; R0603
R28: 100k; R0603
R151, R152: 100k; R0603; TOLERANCE 1%
SW3: SWITCH-ESWITCH-TL3340G; TL3340
U8, U9, U10, U11, U12: MAX9938FEUK; SOT23-5L
U13: STM32F10XCXT6; TQFP-48
U14: LTC2942-1; DFN-6
X1: ECX-2236
X2: ECX-31B

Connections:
A1V5: R20.2, U12.4 (RS-); also elsewhere on the board
A1V5_I: R20.1, U12.5 (RS+); also elsewhere on the board
A1V5_SENSE: U12.3 (OUT), U13.12 (PA2)
A3V3: R19.2, U11.4 (RS-); also elsewhere on the board
A3V3_I: R19.1, U11.5 (RS+); also elsewhere on the board
A3V3_SENSE: U11.3 (OUT), U13.13 (PA3)
AGND: C21.2, C22.2, U9.1 (GND), U9.2 (GND), U10.1 (GND), U10.2 (GND), U11.1 (GND), U11.2 (GND), U12.1 (GND), U12.2 (GND), U13.8 (VSSA); also elsewhere on the board
BOOT0: J7.2, R28.2, U13.44 (BOOT0)
D1V5: R18.2, U10.4 (RS-); also elsewhere on the board
D1V5_I: R18.1, U10.5 (RS+); also elsewhere on the board
D1V5_SENSE: U10.3 (OUT), U13.11 (PA1)
D3V3: R17.2, U9.4 (RS-); also elsewhere on the board
D3V3_I: R17.1, U9.5 (RS+); also elsewhere on the board
D3V3_SENSE: U9.3 (OUT), U13.10 (PA0)
D3V3_STM: C17.1, C18.1, C19.1, C20.1, C21.1, C22.1, J7.1, R22.2, R23.2, U13.1 (VBAT), U13.9 (VDDA), U13.24 (VDD_1), U13.36 (VDD_2), U13.48 (VDD_3); also elsewhere on the board
DGND: C2.1, C3.1, C4.1, C5.1, C15.2, C16.2, C17.2, C18.2, C19.2, C20.2, J7.3, R28.1, R152.1, SW3.1, SW3.3 (1), U8.1 (GND), U8.2 (GND), U13.23 (VSS_1), U13.35 (VSS_2), U13.47 (VSS_3), U14.2 (GND), X1.2 (DGND), X1.4 (DGND); also elsewhere on the board
EXP: U14.EXP
I2C1_SCLI: U13.42 (PB6); also elsewhere on the board
I2C1_SDAI: U13.43 (PB7); also elsewhere on the board
I2C2_SCL: U14.3 (SCL); also elsewhere on the board
I2C2_SCLI: U13.21 (PB10); also elsewhere on the board
I2C2_SDA: U14.4 (SDA); also elsewhere on the board
I2C2_SDAI: U13.22 (PB11); also elsewhere on the board
unnamed: LED2.2 (A), R23.1
unnamed: LED1.2 (A), R22.1
NRST: C16.1, SW3.2, U13.7 (NRST)
OSC_IN: C3.2, U13.5 (OSC_IN), X1.3 (2)
OSC_OUT: C2.2, U13.6 (OSC_OUT), X1.1
PA8: U13.29 (PA8); also elsewhere on the board
PA9: U13.30 (PA9); also elsewhere on the board
PA10: U13.31 (PA10); also elsewhere on the board
PA15: LED1.1 (C), U13.38 (PA15)
PB2: LED2.1 (C), U13.20 (PB2); also elsewhere on the board
PB4: U13.40 (PB4), U14.5 (!AL!/CC); also elsewhere on the board
PB5: U13.41 (PB5); also elsewhere on the board
PB8: U13.45 (PB8); also elsewhere on the board
PB9: U13.46 (PB9); also elsewhere on the board
PC13: U13.2 (PC13); also elsewhere on the board
PC14: R24.1; also elsewhere on the board
PC14-S: C4.2, R24.2, U13.3 (PC14), X2.2
PC15: R25.2; also elsewhere on the board
PC15-S: C5.2, R25.1, U13.4 (PC15), X2.1
SPI1_MISO: U13.16 (PA6); also elsewhere on the board
SPI1_MOSI: U13.17 (PA7); also elsewhere on the board
SPI1_NSS: U13.14 (PA4); also elsewhere on the board
SPI1_SCK: U13.15 (PA5); also elsewhere on the board
SPI2_MISO: U13.27 (PB14); also elsewhere on the board
SPI2_MOSI: U13.28 (PB15); also elsewhere on the board
SPI2_NSS: U13.25 (PB12); also elsewhere on the board
SPI2_SCK: U13.26 (PB13); also elsewhere on the board
SWCLK: U13.37 (PA14); also elsewhere on the board
SWDIO: U13.34 (PA13); also elsewhere on the board
TRACESWO: U13.39 (PB3); also elsewhere on the board
USBDM: U13.32 (PA11); also elsewhere on the board
USBDP: U13.33 (PA12); also elsewhere on the board
VBAT: C15.1, U14.1 (SENSE+); also elsewhere on the board
VBAT_I: U14.6 (SENSE-); also elsewhere on the board
VSUP_I: R16.2, U8.4 (RS-); also elsewhere on the board
VSUP_I_SENSE: U8.3 (OUT), U13.18 (PB0)
VSUP_R: R16.1, R151.2, U8.5 (RS+); also elsewhere on the board
VSUP_V_SENSE: R151.1, R152.2, U13.19 (PB1)

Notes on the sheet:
STM32F102
16 MHz
I2C 1100100
32.768 kHz
